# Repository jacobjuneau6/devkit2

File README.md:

# devkit2

A compact ESP32-S3 development board designed for rapid prototyping and embedded projects.

## Features

- **ESP32-S3-WROOM-1** module — dual-core Xtensa LX7, 2.4 GHz Wi-Fi, BLE 5.0, 8 MB PSRAM, 16 MB Flash
- **USB-C** connector for power, programming, and serial monitor
- **WS2812B** addressable RGB LED on GPIO 2
- **microSD card** slot (TF-PUSH) connected via SPI
- **2× tactile push buttons** — Boot (GPIO 0) and Reset (EN)
- **2× 20-pin breakout headers** bringing out all available GPIO, power rails, and peripheral signals
- **3.3 V LDO regulator** (TPS74533) — up to 500 mA output, 6.5 V max input
- **Compact form factor** — fits on a breadboard with one row of pins free on each side

## Pin Map

```
                    ┌──────────────────┐
             3.3V —│ J1               │— GND
             EN   —│                  │— VIN (5 V)
            IO4   —│                  │— IO5
            IO6   —│                  │— IO7
            IO15  —│                  │— IO8
            IO16  —│                  │— IO9
            IO17  —│                  │— IO10
            IO18  —│                  │— IO11
            IO19  —│                  │— IO12
            IO20  —│                  │— IO13
            IO21  —│    ESP32-S3      │— IO14
            IO26  —│    devkit2       │— IO38
            IO35  —│                  │— IO39
            IO36  —│                  │— IO40
            IO37  —│                  │— IO41
            IO42  —│                  │— IO45
            IO43  —│                  │— IO46
            IO44  —│                  │— IO47
            GND   —│                  │— IO2  (onboard LED)
            5 V   —│                  │— IO0  (Boot button)
                   └──────────────────┘
```

| Peripheral   | GPIO | Notes                         |
|-------------|------|-------------------------------|
| WS2812B LED | 2    | DIN, use NeoPixel lib         |
| Boot button | 0    | Pull LOW to enter download mode |
| Reset button| EN   | Pulls EN pin LOW              |
| microSD CS  | 5    | SPI chip select               |
| microSD MOSI| 11   | SPI data                      |
| microSD MISO| 13   | SPI data                      |
| microSD SCK | 12   | SPI clock                     |

## Getting Started

### 1. Add Board Support

Install the **esp32** board package by Espressif in the Arduino IDE:

1. Open **File → Preferences**
2. Add this URL to **Additional Boards Manager URLs**:
   ```
   https://espressif.github.io/arduino-esp32/package_esp32_index.json
   ```
3. Open **Tools → Board → Boards Manager**, search for `esp32`, and install **esp32 by Espressif Systems**

### 2. Select Board Settings

| Setting          | Value                     |
|-----------------|---------------------------|
| Board            | ESP32S3 Dev Module        |
| USB CDC On Boot  | Enabled                   |
| Flash Size       | 16 MB (128 Mb)            |
| PSRAM            | OPI PSRAM                 |
| Upload Mode      | UART / Hardware CDC       |

### 3. Install Libraries

Install these libraries via **Tools → Manage Libraries**:

- **Adafruit NeoPixel** — for the onboard WS2812B LED
- **SD** (built-in, or **SdFat**) — for the microSD slot

### 4. Upload the Demo

Hold **Boot** (SW1), press and release **Reset** (SW2), then release **Boot** to enter download mode. Open `CODE/demo/demo.ino` in the Arduino IDE, select the correct port, and hit **Upload**.

## Bill of Materials

| Designator | Qty | Value               | Footprint                    | LCSC #    |
|-----------|-----|---------------------|------------------------------|-----------|
| U1        | 1   | ESP32-S3-WROOM-1    | WIRELM-SMD ESP32-S3-WROOM-1 | C2913201  |
| U2        | 1   | TPS74533PCQWDRVRQ1  | WSON-6 2.0×2.0 mm           | C2860924  |
| USB1      | 1   | TYPE-C 16PIN 2MD    | USB-C SMD 16-pin             | C2765186  |
| LED1      | 1   | WS2812B-B/W         | LED-SMD 5.0×5.0 mm           | C2761795  |
| CARD1     | 1   | TF PUSH             | TF-SMD push-push             | C393941   |
| J1, J2    | 2   | PINHD 1×20 Male     | PinHeader 1×20 2.54 mm       | —         |
| SW1, SW2  | 2   | KMR221NGLFS         | KEY-SMD 4.2×2.8 mm           | C269272   |
| R1, R2    | 2   | RT0603BRE075K1L     | 0603 (1608 Metric)           | C728607   |
| R3, R4    | 2   | RT0603BRE0710KL     | 0603 (1608 Metric)           | C6277183  |

- **R1, R2** = 5.1 kΩ thin-film — USB-C CC pull-downs
- **R3, R4** = 10 kΩ thick-film — EN and BOOT pull-ups
- **SW1** = Reset, **SW2** = Boot
- All passives are 0603 imperial (1608 metric)

## Hardware

Board files live in [`BOARD/`](BOARD/). The project was designed in **KiCad 8**.

**🔗 [View schematic & PCB interactively on KiCanvas](https://kicanvas.org/?github=https://github.com/jacobjuneau6/devkit2/blob/main/BOARD/Board/Board.kicad_pro)**

| Directory                 | Contents                     |
|--------------------------|------------------------------|
| `BOARD/Board/`           | Schematic, PCB, project files |
| `BOARD/Board/gbrs/`      | Gerber files (JLCPCB ready)  |
| `BOARD/Board/production/` | BOM, CPL, netlist            |
| `BOARD/CAD/`             | 3D STEP model                |

## License

Hardware and software are released under the [MIT License](LICENSE).

---

Built by [jacobjuneau6](https://github.com/jacobjuneau6)

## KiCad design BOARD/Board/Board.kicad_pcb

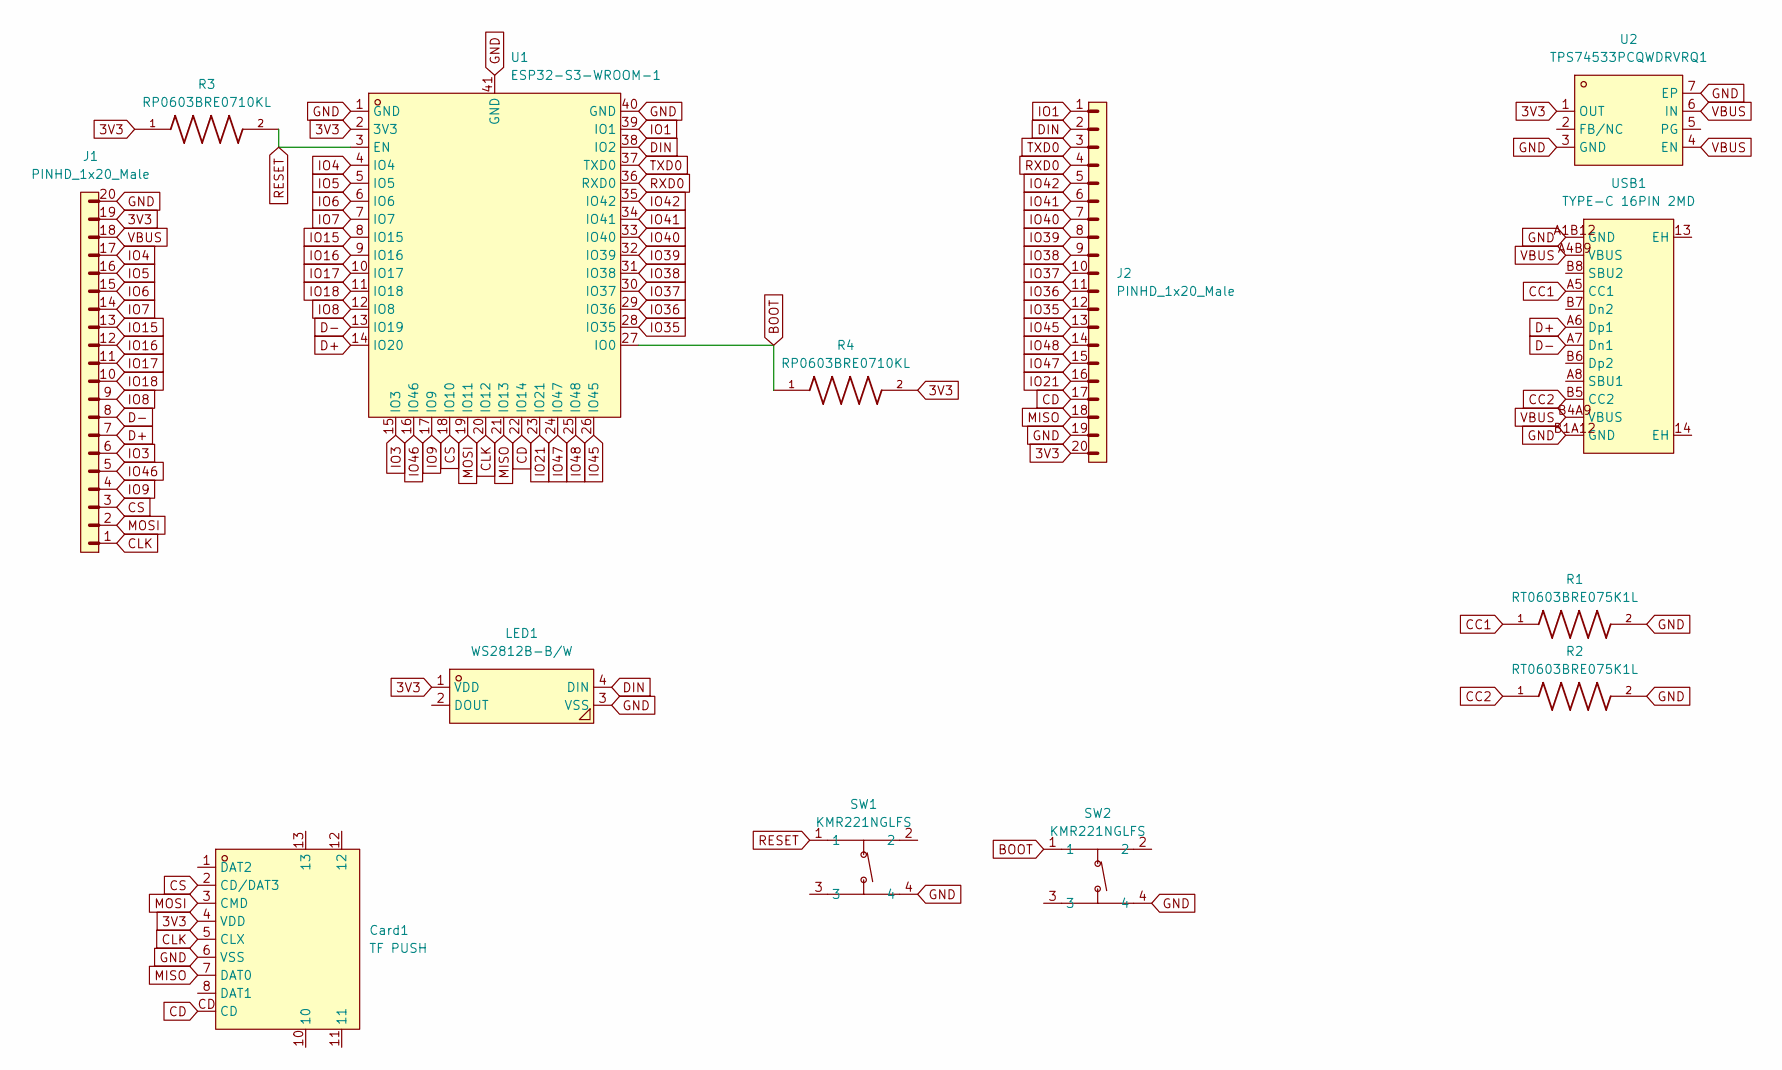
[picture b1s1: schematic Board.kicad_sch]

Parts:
Card1: TF PUSH; TF-SMD_TF-PUSH; MPN TF PUSH; LCSC Part C393941
J1, J2: PINHD_1x20_Male; PinHeader_1x20_P2.54mm_Vertical
LED1: WS2812B-B/W; LED-SMD_4P-L5.0-W5.0-TL_WS2812B-B; MPN WS2812B-B/T; LCSC Part C2761795
R1, R2: RT0603BRE075K1L; RESC1608X55N; MPN TYPE-C 16PIN 2MD(073); LCSC Part C728607
R3, R4: RP0603BRE0710KL; RESC1608X55N; MPN TYPE-C 16PIN 2MD(073); LCSC Part C6277183
SW1, SW2: KMR221NGLFS; KEY-SMD_4P-L4.2-W2.8-P1.60-LS4.6; MPN KMR221NGLFS; LCSC Part C269272
U1: ESP32-S3-WROOM-1; WIRELM-SMD_ESP32-S3-WROOM-1; MPN ESP32-S3-WROOM-1-N8R8; LCSC Part C2913201
U2: TPS74533PCQWDRVRQ1; WSON-6_L2.0-W2.0-P0.65-TL-EP; MPN TPS74533PCQWDRVRQ1; LCSC Part C2860924
USB1: TYPE-C 16PIN 2MD; USB-C-SMD_TYPE-C-16PIN-2MD-073; MPN TYPE-C 16PIN 2MD(073); LCSC Part C2765186

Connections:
3V3: Card1.4 (VDD), J1.19, J2.20, LED1.1 (VDD), R3.1, R4.2, U1.2 (3V3), U2.1 (OUT)
BOOT: R4.1, SW2.1, U1.27 (IO0)
CC1: R1.1, USB1.A5 (CC1)
CC2: R2.1, USB1.B5 (CC2)
CD: Card1.CD, J2.17, U1.22 (IO14)
CLK: Card1.5 (CLX), J1.1, U1.20 (IO12)
CS: Card1.2 (CD/DAT3), J1.3, U1.18 (IO10)
D+: J1.7, U1.14 (IO20), USB1.A6 (Dp1)
D-: J1.8, U1.13 (IO19), USB1.A7 (Dn1)
DIN: J2.2, LED1.4 (DIN), U1.38 (IO2)
GND: Card1.6 (VSS), J1.20, J2.19, LED1.3 (VSS), R1.2, R2.2, SW1.4, SW2.4, U1.1 (GND), U1.40 (GND), U1.41 (GND), U2.3 (GND), U2.7 (EP), USB1.A1B12 (GND), USB1.B1A12 (GND)
IO1: J2.1, U1.39 (IO1)
IO3: J1.6, U1.15 (IO3)
IO4: J1.17, U1.4 (IO4)
IO5: J1.16, U1.5 (IO5)
IO6: J1.15, U1.6 (IO6)
IO7: J1.14, U1.7 (IO7)
IO8: J1.9, U1.12 (IO8)
IO9: J1.4, U1.17 (IO9)
IO15: J1.13, U1.8 (IO15)
IO16: J1.12, U1.9 (IO16)
IO17: J1.11, U1.10 (IO17)
IO18: J1.10, U1.11 (IO18)
IO21: J2.16, U1.23 (IO21)
IO35: J2.12, U1.28 (IO35)
IO36: J2.11, U1.29 (IO36)
IO37: J2.10, U1.30 (IO37)
IO38: J2.9, U1.31 (IO38)
IO39: J2.8, U1.32 (IO39)
IO40: J2.7, U1.33 (IO40)
IO41: J2.6, U1.34 (IO41)
IO42: J2.5, U1.35 (IO42)
IO45: J2.13, U1.26 (IO45)
IO46: J1.5, U1.16 (IO46)
IO47: J2.15, U1.24 (IO47)
IO48: J2.14, U1.25 (IO48)
MISO: Card1.7 (DAT0), J2.18, U1.21 (IO13)
MOSI: Card1.3 (CMD), J1.2, U1.19 (IO11)
RESET: R3.2, SW1.1, U1.3 (EN)
RXD0: J2.4, U1.36 (RXD0)
TXD0: J2.3, U1.37 (TXD0)
VBUS: J1.18, U2.4 (EN), U2.6 (IN), USB1.A4B9 (VBUS), USB1.B4A9 (VBUS)

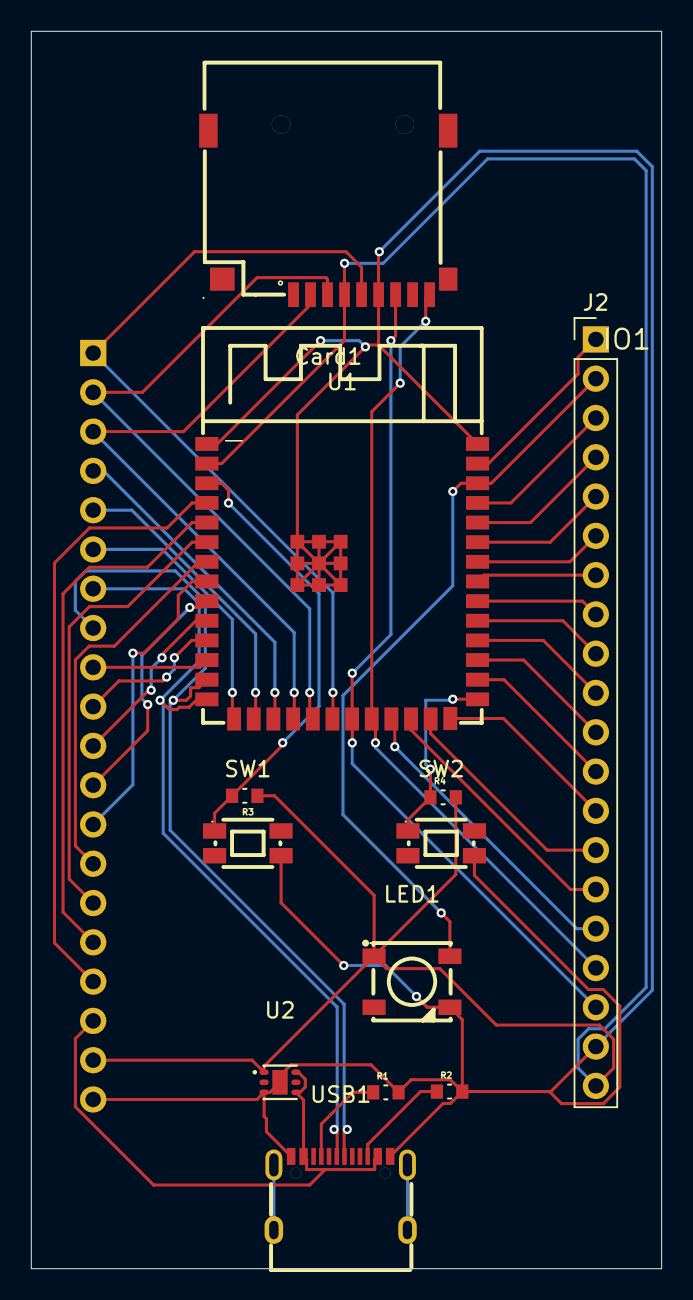
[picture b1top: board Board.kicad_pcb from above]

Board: 2 copper layers, 40.8 x 80.0 mm, 13 parts (1 on the bottom side), 42 nets.

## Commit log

2026-06-29 add pcb, readme & code
2026-06-29 add images
2026-06-29 Update README with corrected links and formatting
2026-06-29 add BOM.csv to main repo
